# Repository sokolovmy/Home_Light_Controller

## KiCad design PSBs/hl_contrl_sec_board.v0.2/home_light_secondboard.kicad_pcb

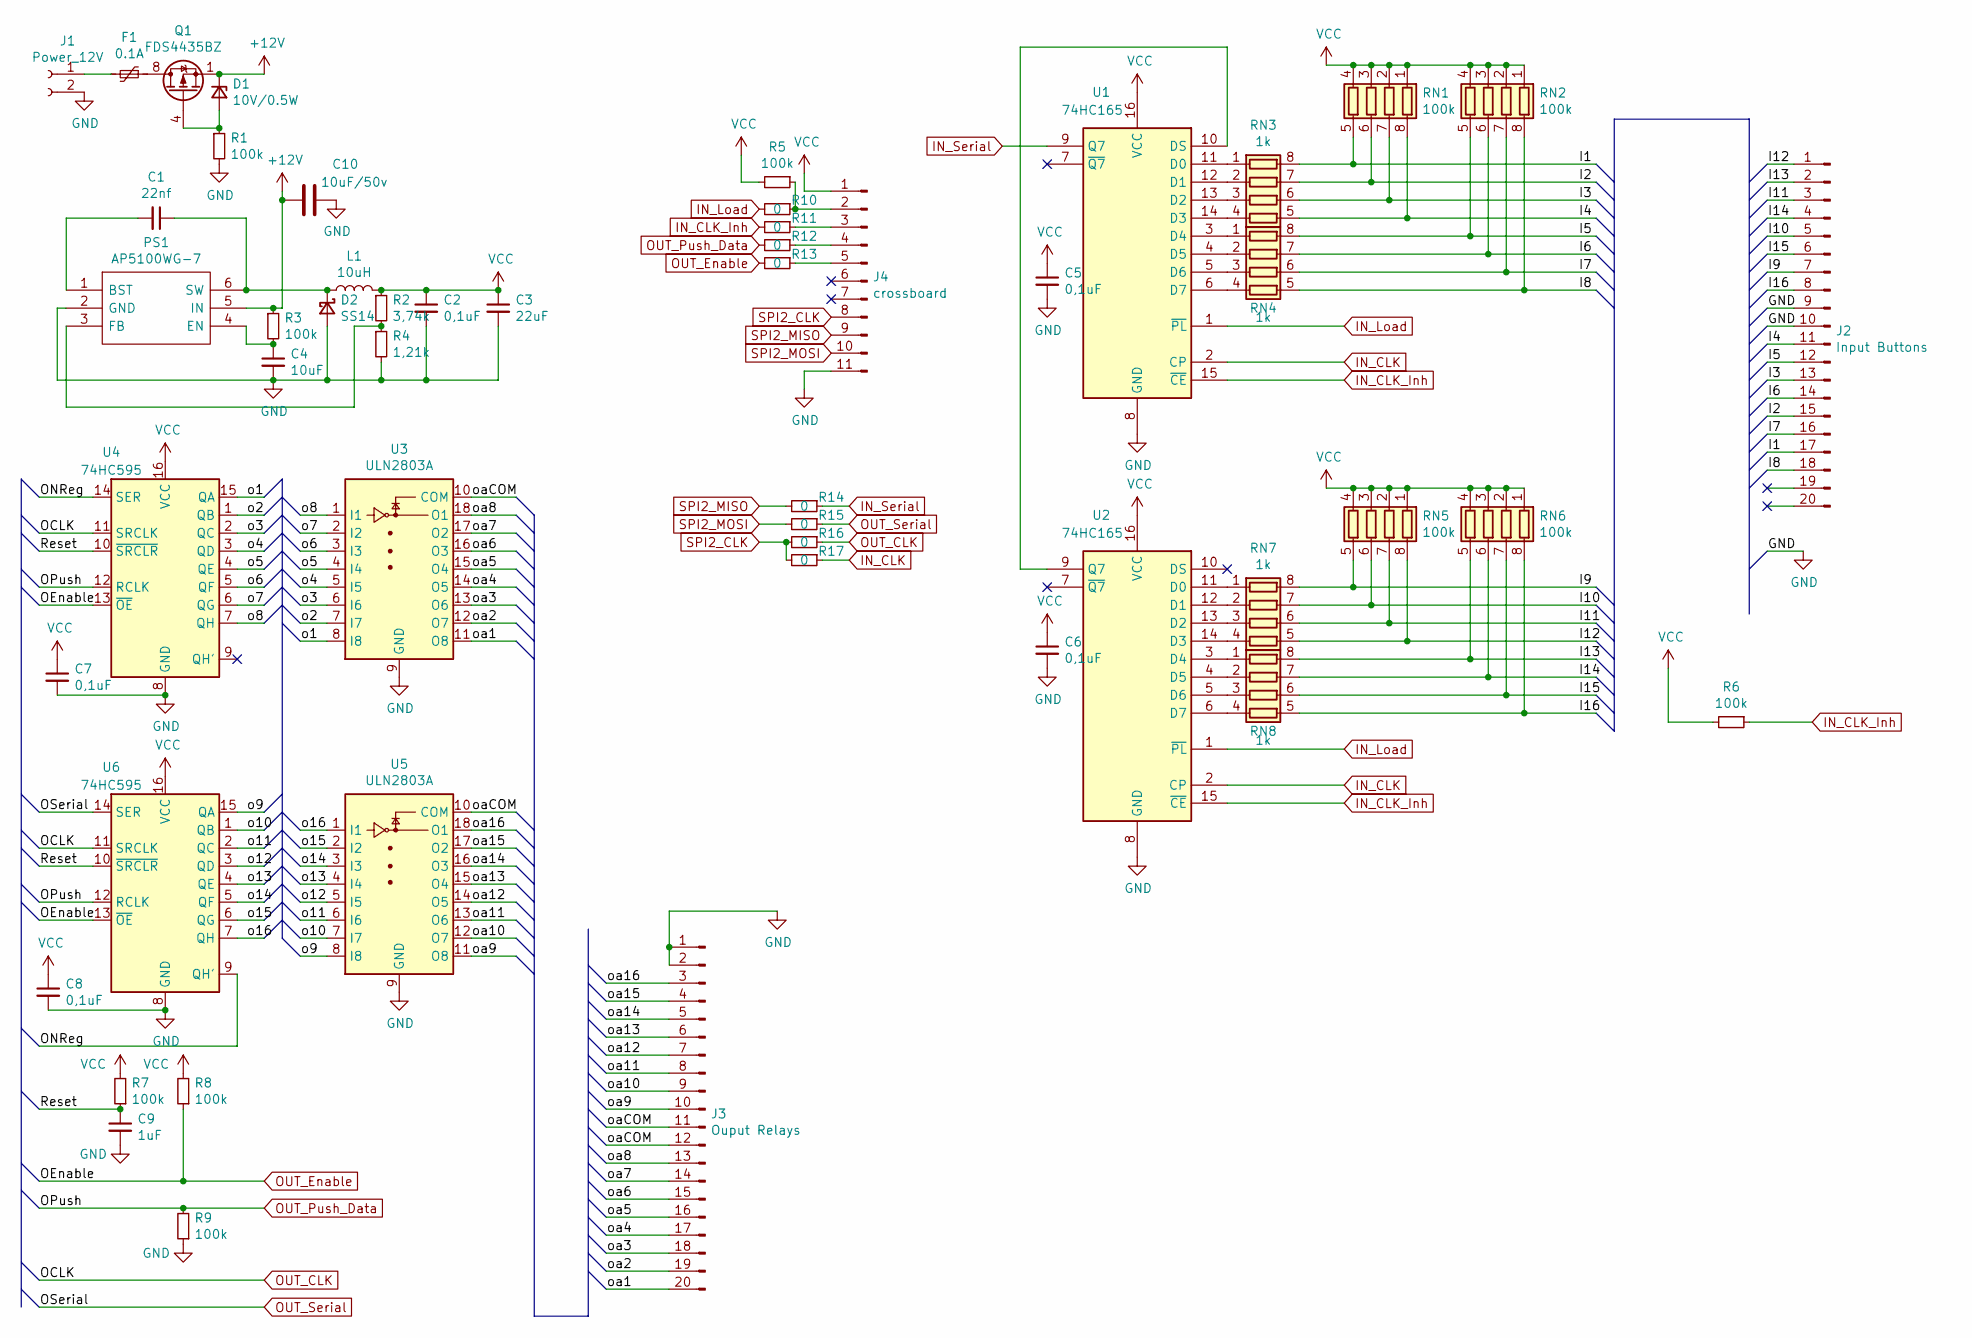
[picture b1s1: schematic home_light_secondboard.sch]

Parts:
C1: 22nf; C_0402_1005Metric_Pad0.74x0.62mm_HandSolder
C2, C5, C6, C7, C8: 0,1uF; C_0603_1608Metric_Pad1.08x0.95mm_HandSolder
C3: 22uF; C_0805_2012Metric_Pad1.18x1.45mm_HandSolder
C4: 10uF; C_0805_2012Metric_Pad1.18x1.45mm_HandSolder
C9: 1uF; C_0805_2012Metric_Pad1.18x1.45mm_HandSolder
C10: 10uF/50v; C_1210_3225Metric_Pad1.33x2.70mm_HandSolder
D1: 10V/0.5W; D_MiniMELF
D2: SS14; D_SMA_Handsoldering
F1: 0.1A; Fuse_1812_4532Metric_Pad1.30x3.40mm_HandSolder
J1: Power_12V; PhoenixContact_MCV_1,5_2-G-5.08_1x02_P5.08mm_Vertical
J2: Input Buttons; IDC-Header_2x10_P2.54mm_Horizontal
J3: Ouput Relays; IDC-Header_2x10_P2.54mm_Horizontal
J4: crossboard; PinHeader_1x11_P2.54mm_Vertical
L1: 10uH; L_Bourns-SRN6028
PS1: AP5100WG-7; SOT95P285X140-6N; Manufacturer_Part_Number AP5100WG-7; Mouser Part Number 621-AP5100WG-7
Q1: FDS4435BZ; SOIC-8_3.9x4.9mm_P1.27mm
R1, R5, R6, R7, R8, R9: 100k; R_0805_2012Metric_Pad1.20x1.40mm_HandSolder
R2: 3,74k; R_0603_1608Metric_Pad0.98x0.95mm_HandSolder
R3: 100k; R_0603_1608Metric_Pad0.98x0.95mm_HandSolder
R4: 1,21k; R_0603_1608Metric_Pad0.98x0.95mm_HandSolder
R10, R11, R12, R13, R14, R15, R16, R17: 0; R_1206_3216Metric_Pad1.30x1.75mm_HandSolder
RN1, RN2, RN5, RN6: 100k; R_Array_Convex_4x0603
RN3, RN4, RN7, RN8: 1k; R_Array_Convex_4x0603
U1, U2: 74HC165; SOIC-16_3.9x9.9mm_P1.27mm
U3, U5: ULN2803A; SOIC-18W_7.5x11.6mm_P1.27mm
U4, U6: 74HC595; TSSOP-16_4.4x5mm_P0.65mm

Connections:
+12V: C10.2, D1.1 (K), PS1.5 (IN), Q1.1 (S), Q1.2 (S), Q1.3 (S), R3.1
/I1: J2.17, RN1.5 (R4.2), RN3.8 (R1.2)
/I2: J2.15, RN1.6 (R3.2), RN3.7 (R2.2)
/I3: J2.13, RN1.7 (R2.2), RN3.6 (R3.2)
/I4: J2.11, RN1.8 (R1.2), RN3.5 (R4.2)
/I5: J2.12, RN2.5 (R4.2), RN4.8 (R1.2)
/I6: J2.14, RN2.6 (R3.2), RN4.7 (R2.2)
/I7: J2.16, RN2.7 (R2.2), RN4.6 (R3.2)
/I8: J2.18, RN2.8 (R1.2), RN4.5 (R4.2)
/I9: J2.7, RN5.5 (R4.2), RN7.8 (R1.2)
/I10: J2.5, RN5.6 (R3.2), RN7.7 (R2.2)
/I11: J2.3, RN5.7 (R2.2), RN7.6 (R3.2)
/I12: J2.1, RN5.8 (R1.2), RN7.5 (R4.2)
/I13: J2.2, RN6.5 (R4.2), RN8.8 (R1.2)
/I14: J2.4, RN6.6 (R3.2), RN8.7 (R2.2)
/I15: J2.6, RN6.7 (R2.2), RN8.6 (R3.2)
/I16: J2.8, RN6.8 (R1.2), RN8.5 (R4.2)
/ONReg: U4.14 (SER), U6.9 (QH')
/Reset: C9.1, R7.1, U4.10 (~SRCLR), U6.10 (~SRCLR)
/o1: U3.8 (I8), U4.15 (QA)
/o2: U3.7 (I7), U4.1 (QB)
/o3: U3.6 (I6), U4.2 (QC)
/o4: U3.5 (I5), U4.3 (QD)
/o5: U3.4 (I4), U4.4 (QE)
/o6: U3.3 (I3), U4.5 (QF)
/o7: U3.2 (I2), U4.6 (QG)
/o8: U3.1 (I1), U4.7 (QH)
/o9: U5.8 (I8), U6.15 (QA)
/o10: U5.7 (I7), U6.1 (QB)
/o11: U5.6 (I6), U6.2 (QC)
/o12: U5.5 (I5), U6.3 (QD)
/o13: U5.4 (I4), U6.4 (QE)
/o14: U5.3 (I3), U6.5 (QF)
/o15: U5.2 (I2), U6.6 (QG)
/o16: U5.1 (I1), U6.7 (QH)
/oa1: J3.20, U3.11 (O8)
/oa2: J3.19, U3.12 (O7)
/oa3: J3.18, U3.13 (O6)
/oa4: J3.17, U3.14 (O5)
/oa5: J3.16, U3.15 (O4)
/oa6: J3.15, U3.16 (O3)
/oa7: J3.14, U3.17 (O2)
/oa8: J3.13, U3.18 (O1)
/oa9: J3.10, U5.11 (O8)
/oa10: J3.9, U5.12 (O7)
/oa11: J3.8, U5.13 (O6)
/oa12: J3.7, U5.14 (O5)
/oa13: J3.6, U5.15 (O4)
/oa14: J3.5, U5.16 (O3)
/oa15: J3.4, U5.17 (O2)
/oa16: J3.3, U5.18 (O1)
/oaCOM: J3.11, J3.12, U3.10 (COM), U5.10 (COM)
GND: C2.2, C3.2, C4.2, C5.2, C6.2, C7.2, C8.2, C9.2, C10.1, D2.2 (A), J1.2, J2.9, J2.10, J3.1, J3.2, J4.11, PS1.2 (GND), R1.2, R4.2, R9.1, U1.8 (GND), U2.8 (GND), U3.9 (GND), U4.8 (GND), U5.9 (GND), U6.8 (GND)
IN_CLK: R17.1, U1.2 (CP), U2.2 (CP)
IN_CLK_Inh: R6.1, R11.2, U1.15 (~CE), U2.15 (~CE)
IN_Load: R10.2, U1.1 (~PL), U2.1 (~PL)
IN_Serial: R14.1, U1.9 (Q7)
unnamed: C1.1, D2.1 (K), L1.1, PS1.6 (SW)
unnamed: C1.2, PS1.1 (BST)
unnamed: C4.1, PS1.4 (EN), R3.2
unnamed: D1.2 (A), Q1.4 (G), R1.1
unnamed: F1.1, Q1.5 (D), Q1.6 (D), Q1.7 (D), Q1.8 (D)
unnamed: F1.2, J1.1
unnamed: J4.2, R5.1, R10.1
unnamed: J4.3, R11.1
unnamed: J4.4, R12.1
unnamed: J4.5, R13.1
unnamed: PS1.3 (FB), R2.2, R4.1
unnamed: RN3.1 (R1.1), U1.11 (D0)
unnamed: RN3.2 (R2.1), U1.12 (D1)
unnamed: RN3.3 (R3.1), U1.13 (D2)
unnamed: RN3.4 (R4.1), U1.14 (D3)
unnamed: RN4.1 (R1.1), U1.3 (D4)
unnamed: RN4.2 (R2.1), U1.4 (D5)
unnamed: RN4.3 (R3.1), U1.5 (D6)
unnamed: RN4.4 (R4.1), U1.6 (D7)
unnamed: RN7.1 (R1.1), U2.11 (D0)
unnamed: RN7.2 (R2.1), U2.12 (D1)
unnamed: RN7.3 (R3.1), U2.13 (D2)
unnamed: RN7.4 (R4.1), U2.14 (D3)
unnamed: RN8.1 (R1.1), U2.3 (D4)
unnamed: RN8.2 (R2.1), U2.4 (D5)
unnamed: RN8.3 (R3.1), U2.5 (D6)
unnamed: RN8.4 (R4.1), U2.6 (D7)
unnamed: U1.10 (DS), U2.9 (Q7)
OUT_CLK: R16.1, U4.11 (SRCLK), U6.11 (SRCLK)
OUT_Enable: R8.1, R13.2, U4.13 (~OE), U6.13 (~OE)
OUT_Push_Data: R9.2, R12.2, U4.12 (RCLK), U6.12 (RCLK)
OUT_Serial: R15.1, U6.14 (SER)
SPI2_CLK: J4.8, R16.2, R17.2
SPI2_MISO: J4.9, R14.2
SPI2_MOSI: J4.10, R15.2
VCC: C2.1, C3.1, C5.1, C6.1, C7.1, C8.1, J4.1, L1.2, R2.1, R5.2, R6.2, R7.2, R8.2, RN1.1 (R1.1), RN1.2 (R2.1), RN1.3 (R3.1), RN1.4 (R4.1), RN2.1 (R1.1), RN2.2 (R2.1), RN2.3 (R3.1), RN2.4 (R4.1), RN5.1 (R1.1), RN5.2 (R2.1), RN5.3 (R3.1), RN5.4 (R4.1), RN6.1 (R1.1), RN6.2 (R2.1), RN6.3 (R3.1), RN6.4 (R4.1), U1.16 (VCC), U2.16 (VCC), U4.16 (VCC), U6.16 (VCC)

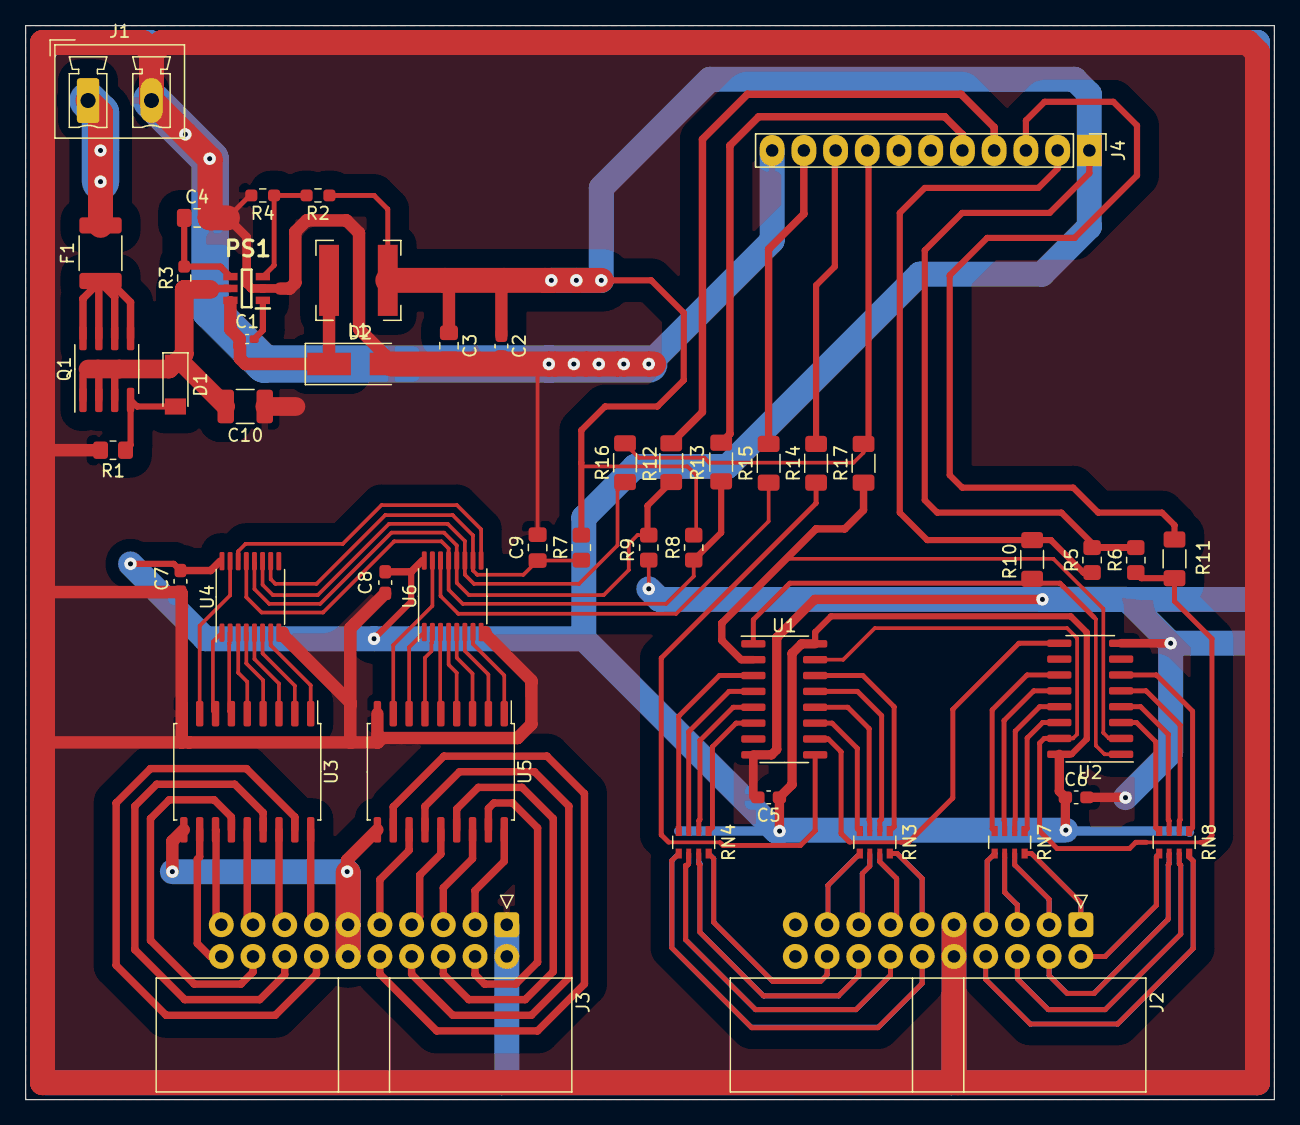
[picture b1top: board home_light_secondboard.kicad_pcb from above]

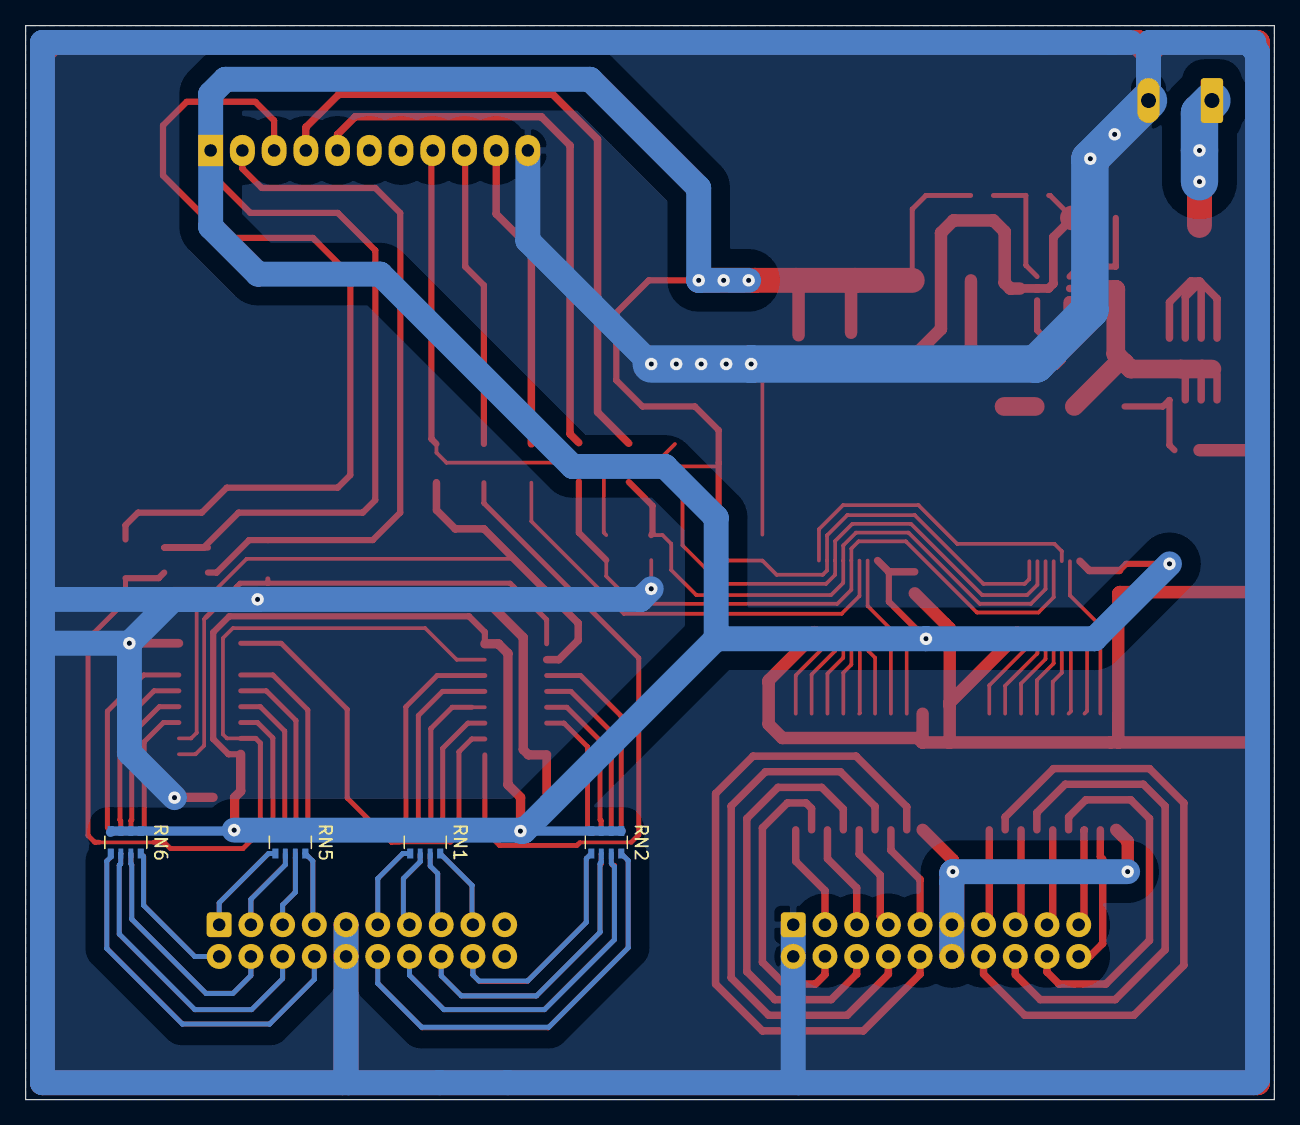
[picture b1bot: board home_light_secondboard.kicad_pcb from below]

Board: 2 copper layers, 100.0 x 86.0 mm, 51 parts (4 on the bottom side), 93 nets.

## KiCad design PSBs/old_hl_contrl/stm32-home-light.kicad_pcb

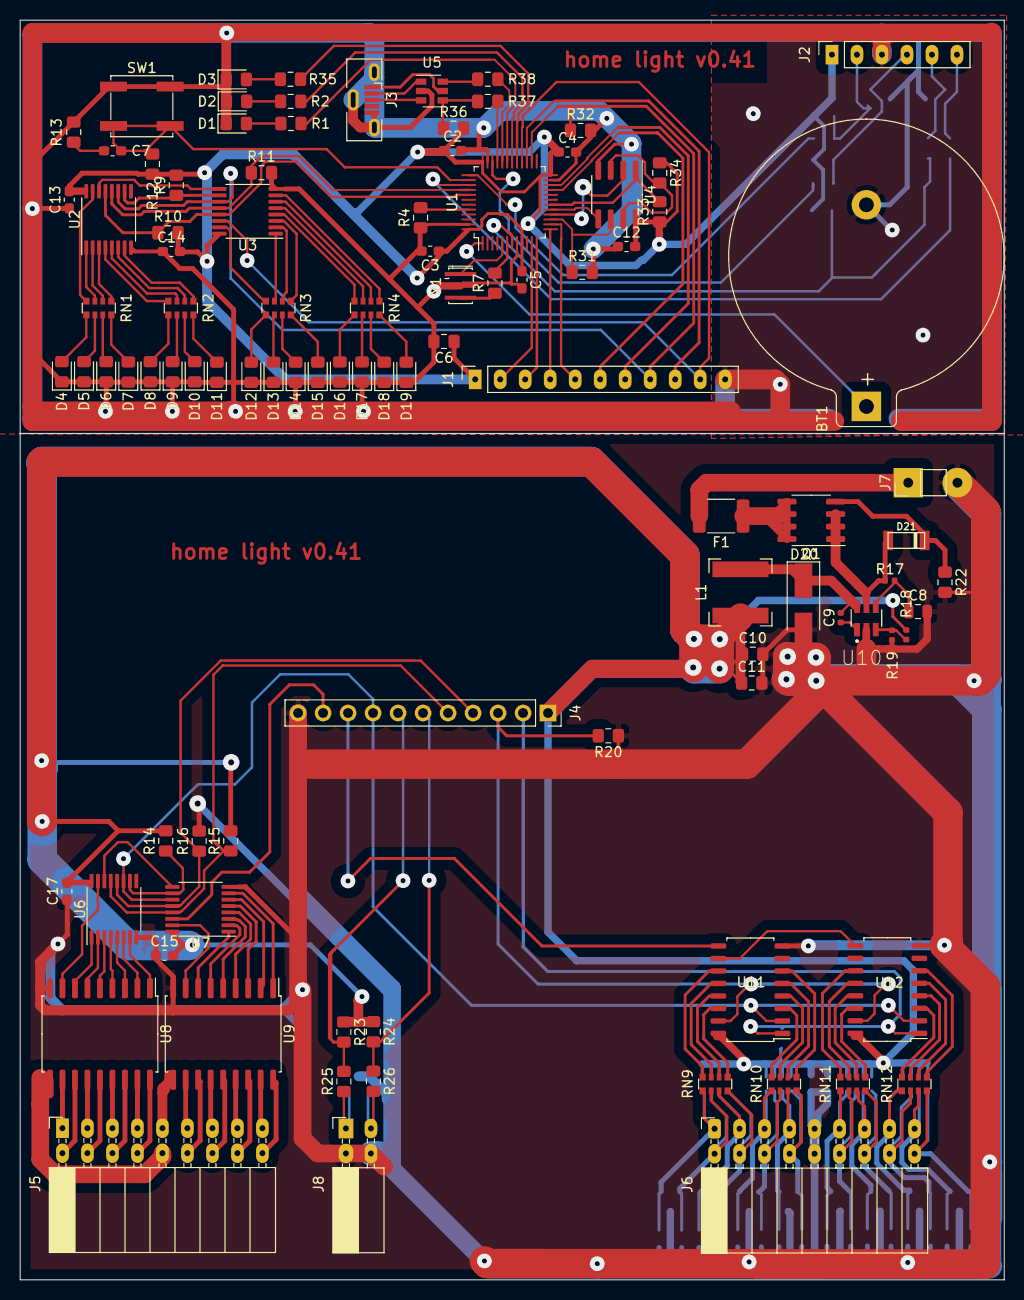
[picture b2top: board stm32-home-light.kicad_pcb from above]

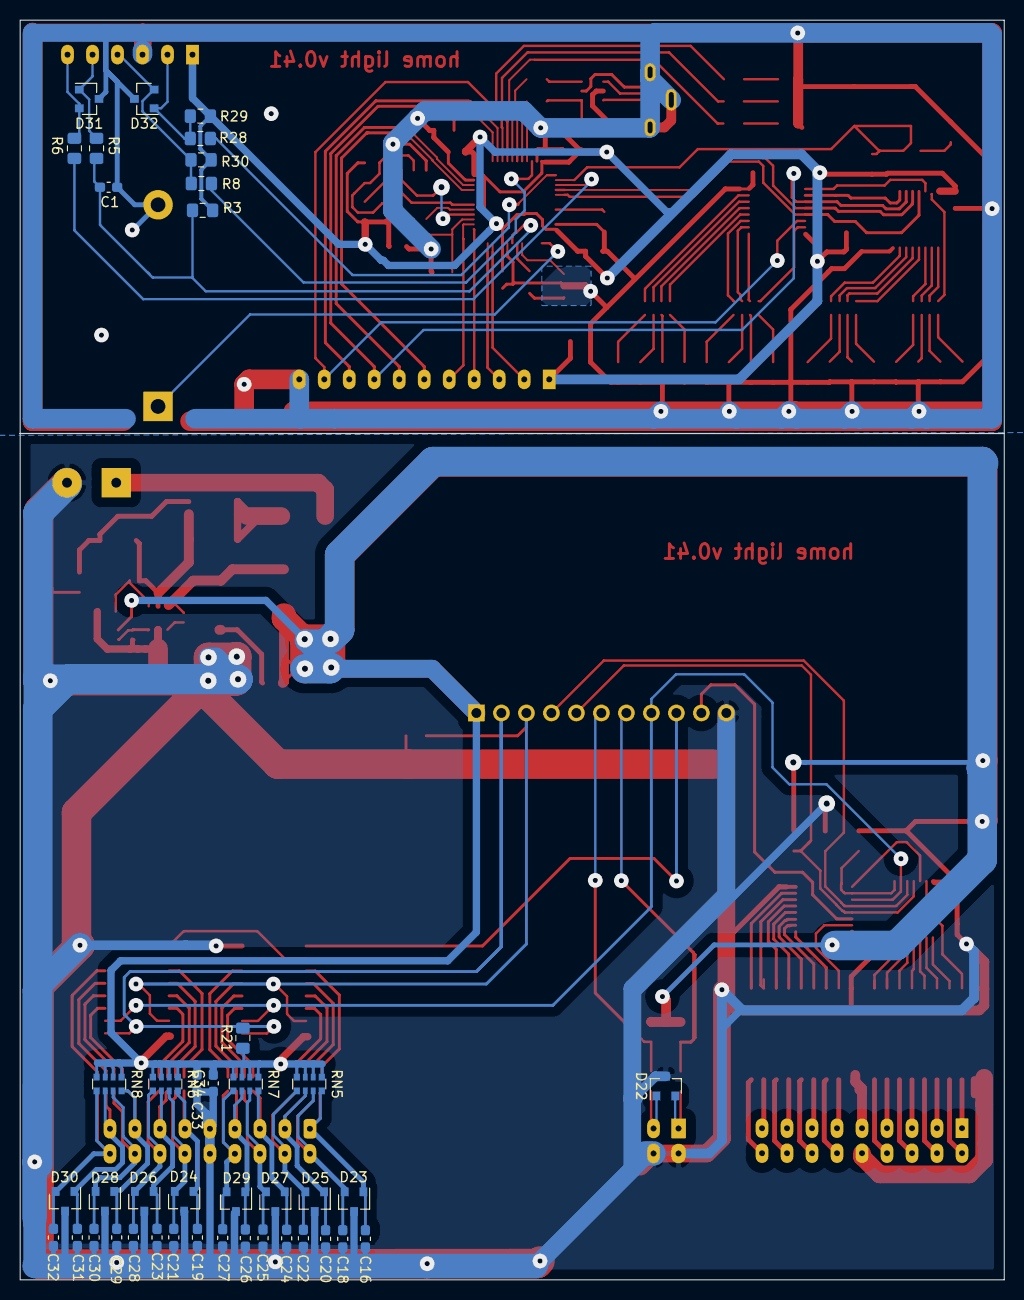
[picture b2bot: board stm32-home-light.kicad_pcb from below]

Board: 2 copper layers, 100.0 x 128.0 mm, 141 parts (42 on the bottom side), 159 nets.

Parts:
BT1: 3v; BatteryHolder_Keystone_106_1x20mm
C1, C2, C3, C4, C5: 0.1uf; C_0603_1608Metric_Pad1.05x0.95mm_HandSolder
C6: 1uf; C_0805_2012Metric_Pad1.15x1.40mm_HandSolder
C7: 100nf; C_0603_1608Metric_Pad1.05x0.95mm_HandSolder
C8: 10uf; C_0805_2012Metric
C9: 22nf; C_0402_1005Metric
C10: 0.1uf; C_0805_2012Metric_Pad1.15x1.40mm_HandSolder
C11: 22uf; C_0805_2012Metric_Pad1.15x1.40mm_HandSolder
C12, C13, C14, C15, C16, C17, C19, C20, C23, C24, C26, C29, C31, C33, C34: 0,1; C_0603_1608Metric_Pad1.05x0.95mm_HandSolder
C18, C21, C22, C25, C27, C28, C30, C32: 0.1; C_0603_1608Metric_Pad1.05x0.95mm_HandSolder
D1, D2, D3: PESD3V3L4UG; LED_0805_2012Metric_Pad1.15x1.40mm_HandSolder
D4: LED1; LED_0805_2012Metric_Pad1.15x1.40mm_HandSolder
D5: LED2; LED_0805_2012Metric_Pad1.15x1.40mm_HandSolder
D6: LED3; LED_0805_2012Metric_Pad1.15x1.40mm_HandSolder
D7: LED4; LED_0805_2012Metric_Pad1.15x1.40mm_HandSolder
D8: LED5; LED_0805_2012Metric_Pad1.15x1.40mm_HandSolder
D9: LED6; LED_0805_2012Metric_Pad1.15x1.40mm_HandSolder
D10: LED7; LED_0805_2012Metric_Pad1.15x1.40mm_HandSolder
D11: LED8; LED_0805_2012Metric_Pad1.15x1.40mm_HandSolder
D12: LED9; LED_0805_2012Metric_Pad1.15x1.40mm_HandSolder
D13: LED10; LED_0805_2012Metric_Pad1.15x1.40mm_HandSolder
D14: LED11; LED_0805_2012Metric_Pad1.15x1.40mm_HandSolder
D15: LED12; LED_0805_2012Metric_Pad1.15x1.40mm_HandSolder
D16: LED13; LED_0805_2012Metric_Pad1.15x1.40mm_HandSolder
D17: LED14; LED_0805_2012Metric_Pad1.15x1.40mm_HandSolder
D18: LED15; LED_0805_2012Metric_Pad1.15x1.40mm_HandSolder
D19: LED16; LED_0805_2012Metric_Pad1.15x1.40mm_HandSolder
D20: SS14; D_SMA_Handsoldering
D21: BZV55-C10; sod80c
D22, D23, D24, D25, D26, D27, D28, D29, D30, D31, D32: PESD3v3S2UT; SOT-23
F1: 0.1A; Fuse_1812_4532Metric_Pad1.30x3.40mm_HandSolder
J1: Crossboard; PinSocket_1x11_P2.54mm_Vertical
J2: Program; PinSocket_1x06_P2.54mm_Vertical
J3: USB_B_Micro; USB_Micro-B_Molex-105133-0001
J4: Crossboard2; PinSocket_1x11_P2.54mm_Vertical
J5: OUT_PORTs; PinSocket_2x09_P2.54mm_Horizontal
J6: IN_Ports; PinSocket_2x09_P2.54mm_Horizontal
J7: Power; PinHeader_1x02_P2.54mm_Vertical
J8: I2C; PinSocket_2x02_P2.54mm_Horizontal
L1: L; L_Bourns-SRN6028
Q1: AO4407A; SOIC-8_3.9x4.9mm_P1.27mm
R1, R2, R7, R35: 1k; R_0805_2012Metric_Pad1.15x1.40mm_HandSolder
R3, R4, R9, R10, R11, R12, R14, R15, R16, R20, R21, R22, R29, R30, R31, R32, R33, R34: 100k; R_0805_2012Metric_Pad1.15x1.40mm_HandSolder
R5, R6, R8, R25, R26, R28, R37, R38: 22; R_0805_2012Metric_Pad1.15x1.40mm_HandSolder
R13: 100; R_0805_2012Metric_Pad1.15x1.40mm_HandSolder
R17: 100k; R_0402_1005Metric
R18: 3.74k; R_0402_1005Metric
R19: 1.21k; R_0402_1005Metric
R23, R24: 10k; R_0805_2012Metric_Pad1.15x1.40mm_HandSolder
R36: 1.5k; R_0805_2012Metric_Pad1.15x1.40mm_HandSolder
RN1, RN2, RN3, RN4: 1k; R_Array_Convex_4x0612_reverse
RN5, RN6, RN7, RN8: 10k; R_Array_Convex_4x0612_reverse
RN9, RN10, RN11, RN12: 1k; R_Array_Convex_4x0612
SW1: BTN; SW_SPST_EVPBF
U1: STM32F103C8Tx; LQFP-48_7x7mm_P0.5mm(lut)
U2, U3, U6, U7: 74HC595; TSSOP-16_4.4x5mm_P0.65mm
U4: M95256-WMN6P; SOIC-8_3.9x4.9mm_P1.27mm
U5: USBLC6-2SC6; SOT-23-6
U8, U9: ULN2803A; SOIC-18W_7.5x11.6mm_P1.27mm
U10: AP5100; SOT26
U11, U12: 74HC165; SOIC-16_4.55x10.3mm_P1.27mm
Y1: 8mhz; Resonator_SMD_muRata_CSTxExxV-3Pin_3.0x1.1mm_HandSoldering

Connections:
/BOOT0: R4.2, U1.44
/Sheet5F465A39/o1: U6.15, U8.8
/Sheet5F465A39/o2: U6.1, U8.7
/Sheet5F465A39/o3: U6.2, U8.6
/Sheet5F465A39/o4: U6.3, U8.5
/Sheet5F465A39/o5: U6.4, U8.4
/Sheet5F465A39/o6: U6.5, U8.3
/Sheet5F465A39/o7: U6.6, U8.2
/Sheet5F465A39/o8: U6.7, U8.1
/Sheet5F465A39/o9: U7.15, U9.8
/Sheet5F465A39/o10: U7.1, U9.7
/Sheet5F465A39/o11: U7.2, U9.6
/Sheet5F465A39/o12: U7.3, U9.5
/Sheet5F465A39/o13: U7.4, U9.4
/Sheet5F465A39/o14: U7.5, U9.3
/Sheet5F465A39/o15: U7.6, U9.2
/Sheet5F465A39/o16: U7.7, U9.1
/Sheet5F465A39/oa1: J5.1, U8.11
/Sheet5F465A39/oa2: J5.2, U8.12
/Sheet5F465A39/oa3: J5.3, U8.13
/Sheet5F465A39/oa4: J5.4, U8.14
/Sheet5F465A39/oa5: J5.5, U8.15
/Sheet5F465A39/oa6: J5.6, U8.16
/Sheet5F465A39/oa7: J5.7, U8.17
/Sheet5F465A39/oa8: J5.8, U8.18
/Sheet5F465A39/oa9: J5.11, U9.11
/Sheet5F465A39/oa10: J5.12, U9.12
/Sheet5F465A39/oa11: J5.13, U9.13
/Sheet5F465A39/oa12: J5.14, U9.14
/Sheet5F465A39/oa13: J5.15, U9.15
/Sheet5F465A39/oa14: J5.16, U9.16
/Sheet5F465A39/oa15: J5.17, U9.17
/Sheet5F465A39/oa16: J5.18, U9.18
/Sheet5F465A39/oac1: J5.10, U8.10
/Sheet5F465A39/oac2: J5.9, U9.10
BTN: C7.1, R12.2, SW1.2, U1.38
EEPROM_SELECT: R33.2, U1.18, U4.1
GND: BT1.2, C1.2, C2.2, C3.2, C4.2, C5.2, C6.2, C8.2, C10.2, C11.2, C12.1, C13.1, C14.1, C15.1, C16.2, C17.1, C18.2, C19.2, C20.2, C21.2, C22.2, C23.2, C24.2, C25.2, C26.2, C27.2, C28.2, C29.2, C30.2, C31.2, C32.2, C33.1, C34.1, D1.1, D2.1, D3.1, D4.1, D5.1, D6.1, D7.1, D8.1, D9.1, D10.1, D11.1, D12.1, D13.1, D14.1, D15.1, D16.1, D17.1, D18.1, D19.1, D20.2, D22.3, D23.3, D24.3, D25.3, D26.3, D27.3, D28.3, D29.3, D30.3, D31.3, D32.3, J1.11, J2.3, J3.5, J3.6, J4.11, J6.9, J6.10, J7.2, J8.2, J8.4, R4.1, R11.2, R13.1, R16.2, R19.2, R20.1, R22.2, R31.2, R32.2, SW1.1, U1.8, U1.23, U1.35, U1.47, U2.8, U3.8, U4.4, U5.2, U6.8, U7.8, U8.9, U9.9, U10.2, U11.8, U12.8, Y1.2
I2C2_SCL: J1.6, J4.6, R24.2, R26.1, U1.21
I2C2_SDA: J1.7, J4.7, R23.2, R25.2, U1.22
IN_CLK: J1.8, J4.8, R32.1, U1.26, U2.11, U3.11, U6.11, U7.11, U11.2, U12.2
IN_CLK_Inhibit: J1.3, J4.3, R20.2, U1.12, U11.15, U12.15
IN_SER: J1.9, J4.9, U1.27, U11.9
IN_Shift_Load: J1.2, J4.2, R21.2, U1.11, U11.1, U12.1
LED_Enable: R10.1, U1.41, U2.13, U3.13
LED_GREEN: R35.1, U1.29
LED_Push_Data: R11.1, U1.40, U2.12, U3.12
LED_RED: R1.1, U1.31
LED_Ser: J1.10, J4.10, U1.28, U3.14, U7.14
LED_YELLOW: R2.1, U1.30
NRST: D31.1, J2.5, R5.1
unnamed: BT1.1, U1.1
unnamed: C1.1, R3.1, R5.2, U1.7
unnamed: C7.2, R13.2
unnamed: C8.1, R17.2, U10.4
unnamed: C9.1, U10.1
unnamed: C9.2, D20.1, L1.1, U10.6
unnamed: C16.1, D23.1, J6.1, RN5.5, RN9.1
unnamed: C18.1, D23.2, J6.2, RN5.6, RN9.2
unnamed: C19.1, D24.1, J6.11, RN6.5, RN11.1
unnamed: C20.1, D25.1, J6.3, RN5.7, RN9.3
unnamed: C21.1, D24.2, J6.12, RN6.6, RN11.2
unnamed: C22.1, D25.2, J6.4, RN5.8, RN9.4
unnamed: C23.1, D26.1, J6.13, RN6.7, RN11.3
unnamed: C24.1, D27.1, J6.5, RN7.5, RN10.1
unnamed: C25.1, D27.2, J6.6, RN7.6, RN10.2
unnamed: C26.1, D29.1, J6.7, RN7.7, RN10.3
unnamed: C27.1, D29.2, J6.8, RN7.8, RN10.4
unnamed: C28.1, D26.2, J6.14, RN6.8, RN11.4
unnamed: C29.1, D28.1, J6.15, RN8.5, RN12.1
unnamed: C30.1, D28.2, J6.16, RN8.6, RN12.2
unnamed: C31.1, D30.1, J6.17, RN8.7, RN12.3
unnamed: C32.1, D30.2, J6.18, RN8.8, RN12.4
unnamed: D1.2, R1.2
unnamed: D2.2, R2.2
unnamed: D3.2, R35.2
unnamed: D4.2, RN1.8
unnamed: D5.2, RN1.7
unnamed: D6.2, RN1.6
unnamed: D7.2, RN1.5
unnamed: D8.2, RN2.8
unnamed: D9.2, RN2.7
unnamed: D10.2, RN2.6
unnamed: D11.2, RN2.5
unnamed: D12.2, RN3.8
unnamed: D13.2, RN3.7
unnamed: D14.2, RN3.6
unnamed: D15.2, RN3.5
unnamed: D16.2, RN4.8
unnamed: D17.2, RN4.7
unnamed: D18.2, RN4.6
unnamed: D19.2, RN4.5
unnamed: D21.1, Q1.1, Q1.2, Q1.3, R17.1, U10.5
unnamed: D21.2, Q1.4, R22.1
unnamed: D22.1, J8.3, R26.2
unnamed: D22.2, J8.1, R25.1
unnamed: F1.1, Q1.5, Q1.6, Q1.7, Q1.8
unnamed: F1.2, J7.1
unnamed: J3.1, U5.5
unnamed: J3.2, U5.1
unnamed: J3.3, U5.3
unnamed: R6.1, U1.39
unnamed: R7.1, Y1.3
unnamed: R7.2, U1.6
unnamed: R8.1, U1.34
unnamed: R9.1, U2.10, U3.10
unnamed: R14.1, U6.10, U7.10
unnamed: R18.2, R19.1, U10.3
unnamed: R28.1, U1.37
unnamed: R34.2, U4.3, U4.7
unnamed: R36.1, R37.2, U5.4
unnamed: R38.2, U5.6
unnamed: RN1.1, U2.15
unnamed: RN1.2, U2.1
unnamed: RN1.3, U2.2
unnamed: RN1.4, U2.3
unnamed: RN2.1, U2.4
unnamed: RN2.2, U2.5
unnamed: RN2.3, U2.6
unnamed: RN2.4, U2.7
unnamed: RN3.1, U3.15
unnamed: RN3.2, U3.1
unnamed: RN3.3, U3.2
unnamed: RN3.4, U3.3
unnamed: RN4.1, U3.4
unnamed: RN4.2, U3.5
unnamed: RN4.3, U3.6
unnamed: RN4.4, U3.7
unnamed: RN9.5, U11.14
unnamed: RN9.6, U11.13
unnamed: RN9.7, U11.12
unnamed: RN9.8, U11.11
unnamed: RN10.5, U11.6
unnamed: RN10.6, U11.5
unnamed: RN10.7, U11.4
unnamed: RN10.8, U11.3
unnamed: RN11.5, U12.14
unnamed: RN11.6, U12.13
unnamed: RN11.7, U12.12
unnamed: RN11.8, U12.11
unnamed: RN12.5, U12.6
unnamed: RN12.6, U12.5
unnamed: RN12.7, U12.4
unnamed: RN12.8, U12.3
unnamed: U1.5, Y1.1
unnamed: U2.14, U3.9
unnamed: U6.14, U7.9
unnamed: U11.10, U12.9
OUT_Enable: J1.5, J4.5, R15.1, U1.14, U6.13, U7.13
OUT_Push_Data: J1.4, J4.4, R16.1, U1.13, U6.12, U7.12
SPI1_CLK: R31.1, U1.15, U4.6
SPI1_MISO: U1.16, U4.2
SPI1_MOSI: U1.17, U4.5
SWCLK: D32.1, J2.2, R28.2, R29.2
SWDIO: D32.2, J2.4, R8.2, R30.2
SWO: D31.2, J2.6, R6.2
USB+: R37.1, U1.33
USB-: R38.1, U1.32
VCC: C2.1, C3.1, C4.1, C5.1, C6.1, C10.1, C11.1, C12.2, C13.2, C14.2, C15.2, C17.2, C33.2, C34.2, J1.1, J2.1, J4.1, L1.2, R3.2, R9.2, R10.2, R12.1, R14.2, R15.2, R18.1, R21.1, R23.1, R24.1, R29.1, R30.1, R33.1, R34.1, R36.2, RN5.1, RN5.2, RN5.3, RN5.4, RN6.1, RN6.2, RN6.3, RN6.4, RN7.1, RN7.2, RN7.3, RN7.4, RN8.1, RN8.2, RN8.3, RN8.4, U1.9, U1.24, U1.36, U1.48, U2.16, U3.16, U4.8, U6.16, U7.16, U11.16, U12.16

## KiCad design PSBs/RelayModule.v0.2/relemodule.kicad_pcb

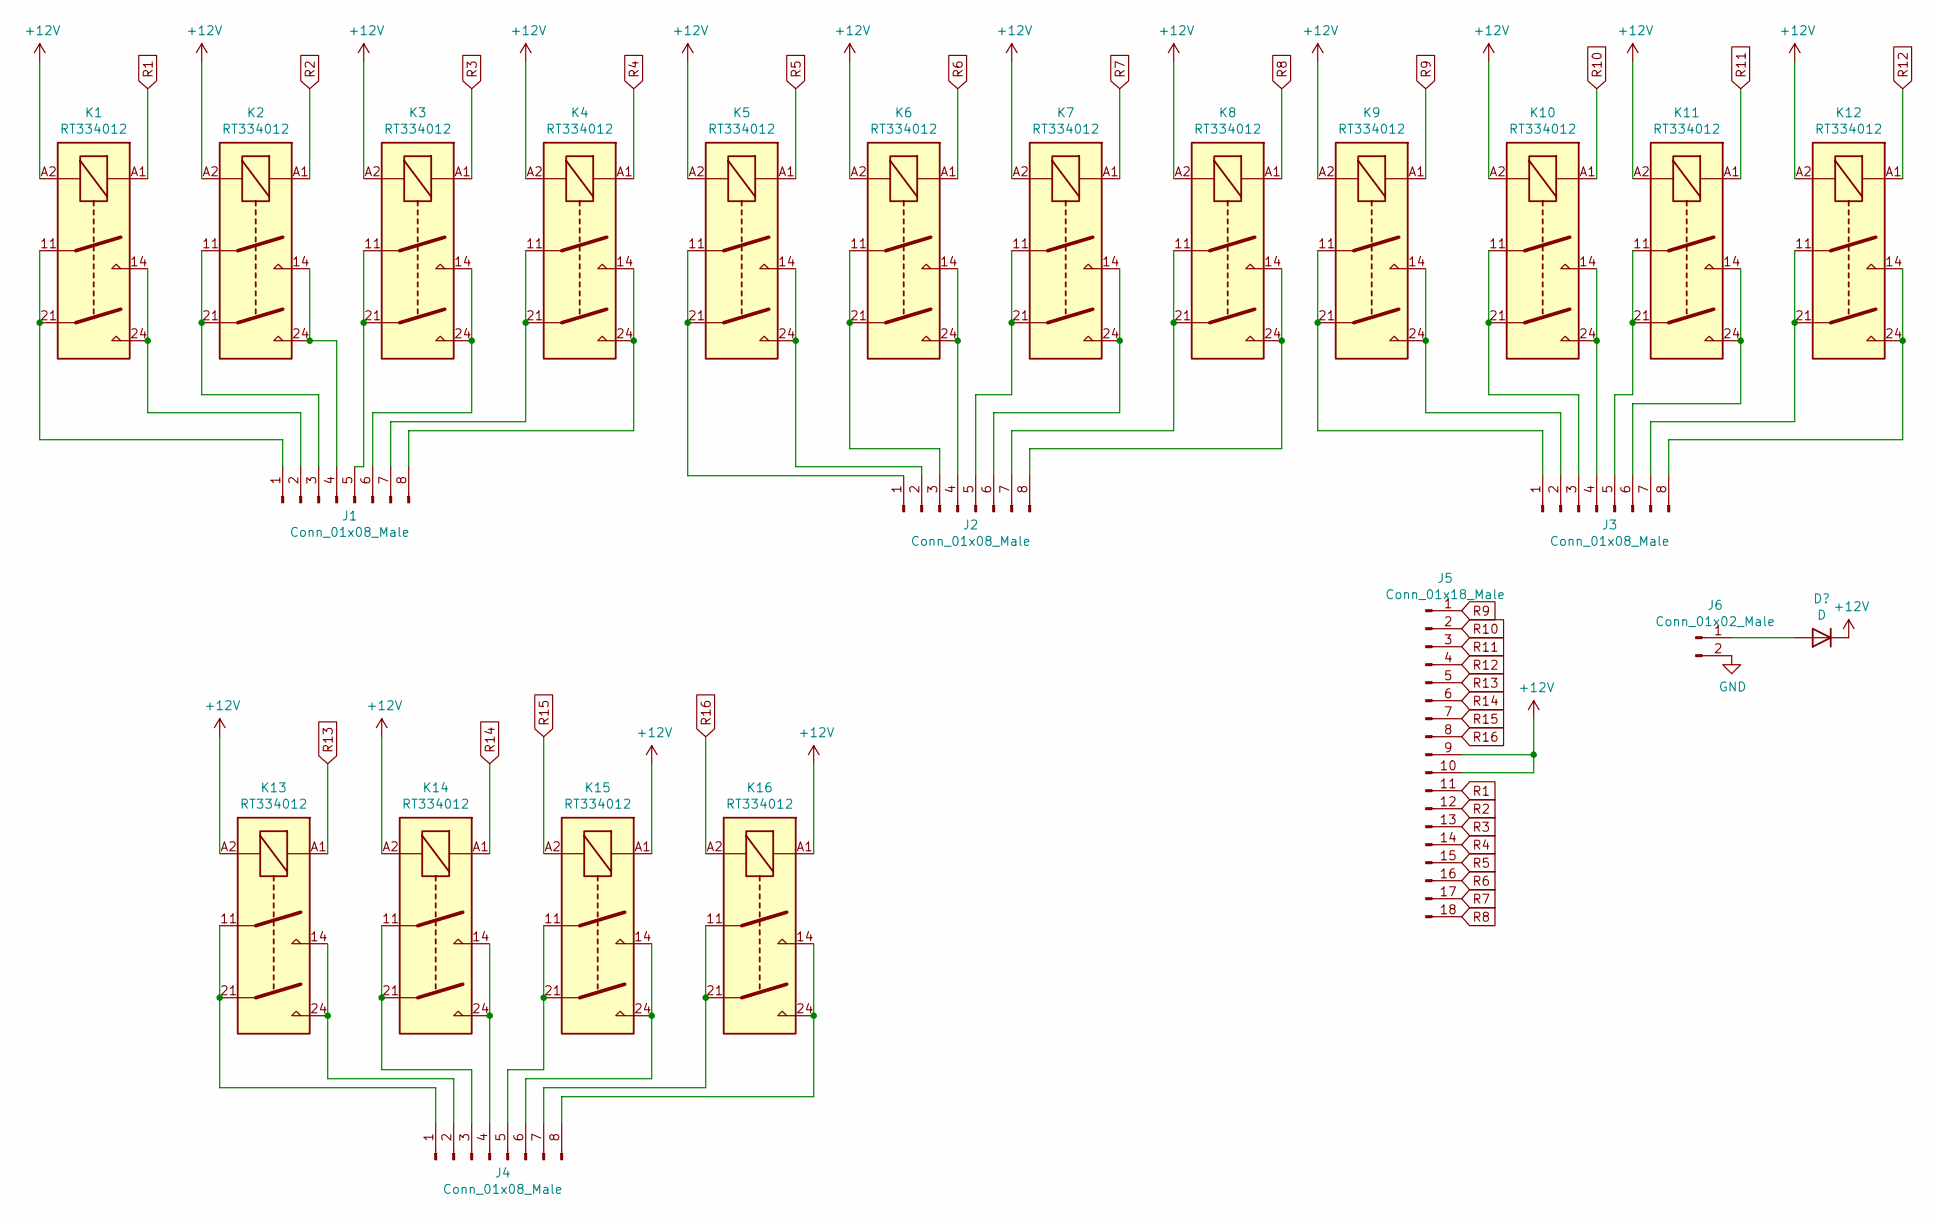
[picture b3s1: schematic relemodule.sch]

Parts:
J1, J2, J3, J4: Conn_01x08_Male; PhoenixContact_MCV_1,5_8-G-5.08_1x08_P5.08mm_Vertical
J5: Conn_01x18_Male; PinSocket_2x09_P2.54mm_Horizontal
J6: Conn_01x02_Male; PhoenixContact_MCV_1,5_2-G-5.08_1x02_P5.08mm_Vertical
K1, K2, K3, K4, K5, K6, K7, K8, K9, K10, K11, K12, K13, K14, K15, K16: RT334012; Relay_DPST_Schrack-RT2-FormA_RM5mm

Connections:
+12V: J5.9, J5.10, J6.1, K1.A2, K2.A2, K3.A2, K4.A2, K5.A2, K6.A2, K7.A2, K8.A2, K9.A2, K10.A2, K11.A2, K12.A2, K13.A2, K14.A2, K15.A1, K16.A1
GND: J6.2
unnamed: J1.1, K1.11, K1.21
unnamed: J1.2, K1.14, K1.24
unnamed: J1.3, K2.11, K2.21
unnamed: J1.4, K2.14, K2.24
unnamed: J1.5, K3.11, K3.21
unnamed: J1.6, K3.14, K3.24
unnamed: J1.7, K4.11, K4.21
unnamed: J1.8, K4.14, K4.24
unnamed: J2.1, K5.11, K5.21
unnamed: J2.2, K5.14, K5.24
unnamed: J2.3, K6.11, K6.21
unnamed: J2.4, K6.14, K6.24
unnamed: J2.5, K7.11, K7.21
unnamed: J2.6, K7.14, K7.24
unnamed: J2.7, K8.11, K8.21
unnamed: J2.8, K8.14, K8.24
unnamed: J3.1, K9.11, K9.21
unnamed: J3.2, K9.14, K9.24
unnamed: J3.3, K10.11, K10.21
unnamed: J3.4, K10.14, K10.24
unnamed: J3.5, K11.11, K11.21
unnamed: J3.6, K11.14, K11.24
unnamed: J3.7, K12.11, K12.21
unnamed: J3.8, K12.14, K12.24
unnamed: J4.1, K13.11, K13.21
unnamed: J4.2, K13.14, K13.24
unnamed: J4.3, K14.11, K14.21
unnamed: J4.4, K14.14, K14.24
unnamed: J4.5, K15.11, K15.21
unnamed: J4.6, K15.14, K15.24
unnamed: J4.7, K16.11, K16.21
unnamed: J4.8, K16.14, K16.24
R1: J5.11, K1.A1
R2: J5.12, K2.A1
R3: J5.13, K3.A1
R4: J5.14, K4.A1
R5: J5.15, K5.A1
R6: J5.16, K6.A1
R7: J5.17, K7.A1
R8: J5.18, K8.A1
R9: J5.1, K9.A1
R10: J5.2, K10.A1
R11: J5.3, K11.A1
R12: J5.4, K12.A1
R13: J5.5, K13.A1
R14: J5.6, K14.A1
R15: J5.7, K15.A2
R16: J5.8, K16.A2

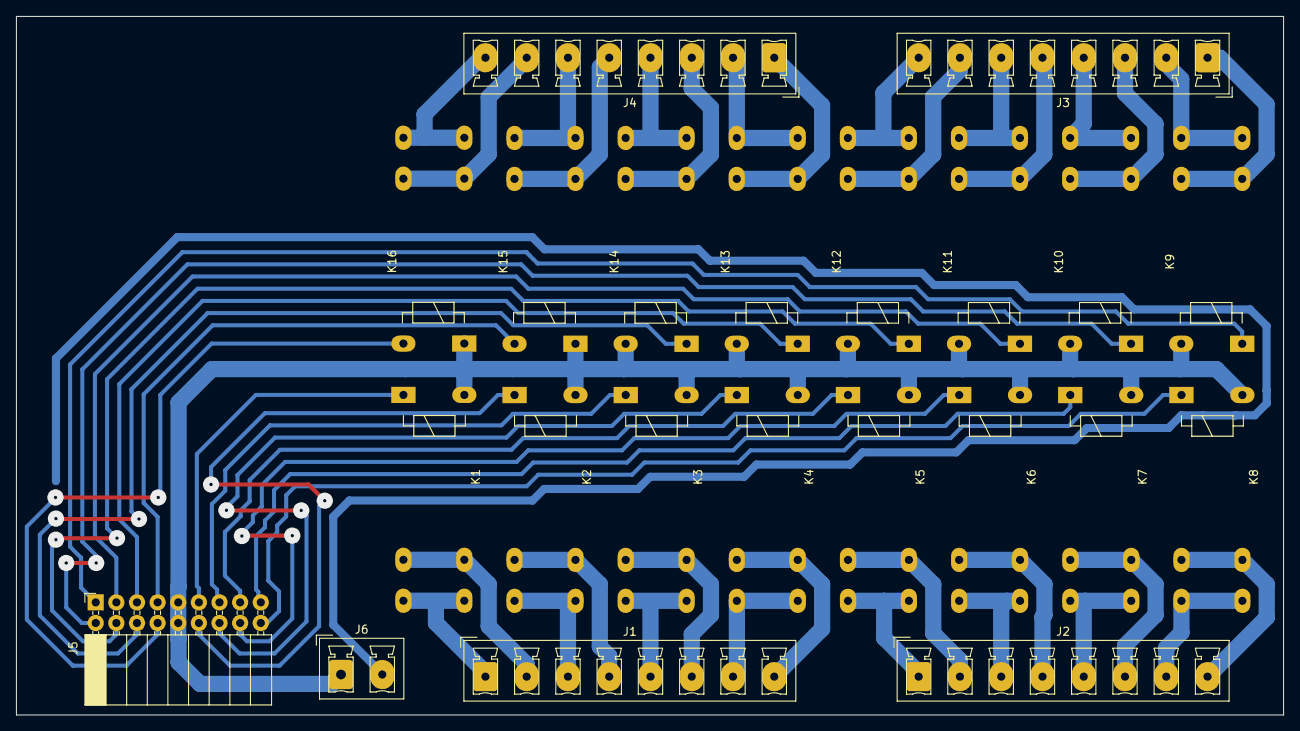
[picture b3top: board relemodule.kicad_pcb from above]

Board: 2 copper layers, 156.0 x 86.0 mm, 22 parts (0 on the bottom side), 49 nets.

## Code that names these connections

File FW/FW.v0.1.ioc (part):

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Mcu.Name=STM32F103C(8-B)Tx
Mcu.Package=LQFP48
Mcu.UserName=STM32F103C8Tx
PA1.GPIOParameters=GPIO_Label
PA1.GPIO_Label=IN_LOAD
PA1.Signal=GPIO_Output
PA10.GPIOParameters=GPIO_Label
PA10.GPIO_Label=LED_RED
PA10.Signal=GPIO_Output
PA11.Mode=Device
PA11.Signal=USB_DM
PA12.Mode=Device
PA12.Signal=USB_DP
PA13.Mode=Trace_Asynchronous_SW
PA13.Signal=SYS_JTMS-SWDIO
PA14.Mode=Trace_Asynchronous_SW
PA14.Signal=SYS_JTCK-SWCLK
PA15.GPIOParameters=GPIO_Label
PA15.GPIO_Label=BTN
PA15.Signal=GPIO_Input
PA2.GPIOParameters=GPIO_Label
PA2.GPIO_Label=IN_CLK_INH
PA2.Signal=GPIO_Output
PA3.GPIOParameters=GPIO_Label
PA3.GPIO_Label=OUT_PUSH_DATA
PA3.Signal=GPIO_Output
PA4.GPIOParameters=PinState,GPIO_Label
PA4.GPIO_Label=OUT_ENABLE
PA4.PinState=GPIO_PIN_SET
PA4.Signal=GPIO_Output
PA5.Mode=Full_Duplex_Master
PA5.Signal=SPI1_SCK
PA6.Mode=Full_Duplex_Master
PA6.Signal=SPI1_MISO
PA7.Mode=Full_Duplex_Master
PA7.Signal=SPI1_MOSI
PA8.GPIOParameters=GPIO_Label
PA8.GPIO_Label=LED_GREEN
PA8.Signal=GPIO_Output
PA9.GPIOParameters=GPIO_Label
PA9.GPIO_Label=LED_YELLOW
PA9.Signal=GPIO_Output
PB0.GPIOParameters=GPIO_Label
PB0.GPIO_Label=EEPROM_CS
PB0.Signal=GPIO_Output
PB13.Mode=Full_Duplex_Master
PB13.Signal=SPI2_SCK
PB14.Mode=Full_Duplex_Master
PB14.Signal=SPI2_MISO
PB15.Mode=Full_Duplex_Master
PB15.Signal=SPI2_MOSI
PB3.Mode=Trace_Asynchronous_SW
PB3.Signal=SYS_JTDO-TRACESWO
PB4.GPIOParameters=GPIO_Label
PB4.GPIO_Label=LED_PUSH_DATA
PB4.Signal=GPIO_Output
PB5.GPIOParameters=PinState,GPIO_Label
PB5.GPIO_Label=LED_ENABLE
PB5.PinState=GPIO_PIN_SET
PB5.Signal=GPIO_Output
PD0-OSC_IN.Mode=HSE-External-Oscillator
PD0-OSC_IN.Signal=RCC_OSC_IN
PD1-OSC_OUT.Mode=HSE-External-Oscillator
PD1-OSC_OUT.Signal=RCC_OSC_OUT
RCC.SYSCLKFreq_VALUE=72000000
RCC.SYSCLKSource=RCC_SYSCLKSOURCE_PLLCLK
board=custom
